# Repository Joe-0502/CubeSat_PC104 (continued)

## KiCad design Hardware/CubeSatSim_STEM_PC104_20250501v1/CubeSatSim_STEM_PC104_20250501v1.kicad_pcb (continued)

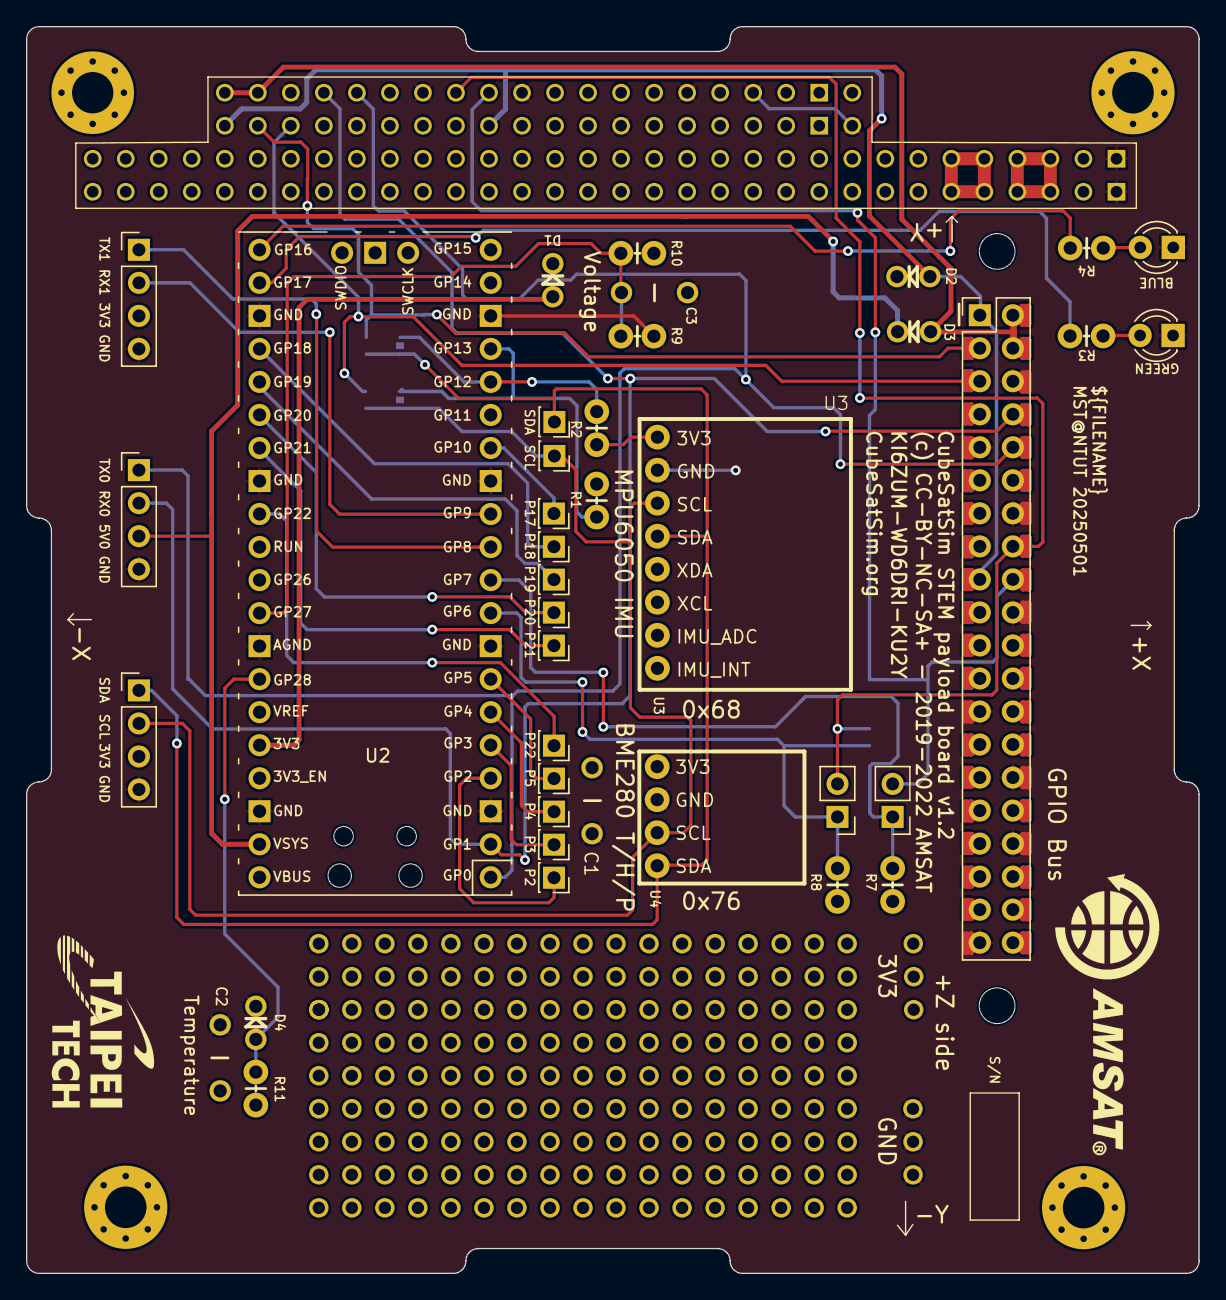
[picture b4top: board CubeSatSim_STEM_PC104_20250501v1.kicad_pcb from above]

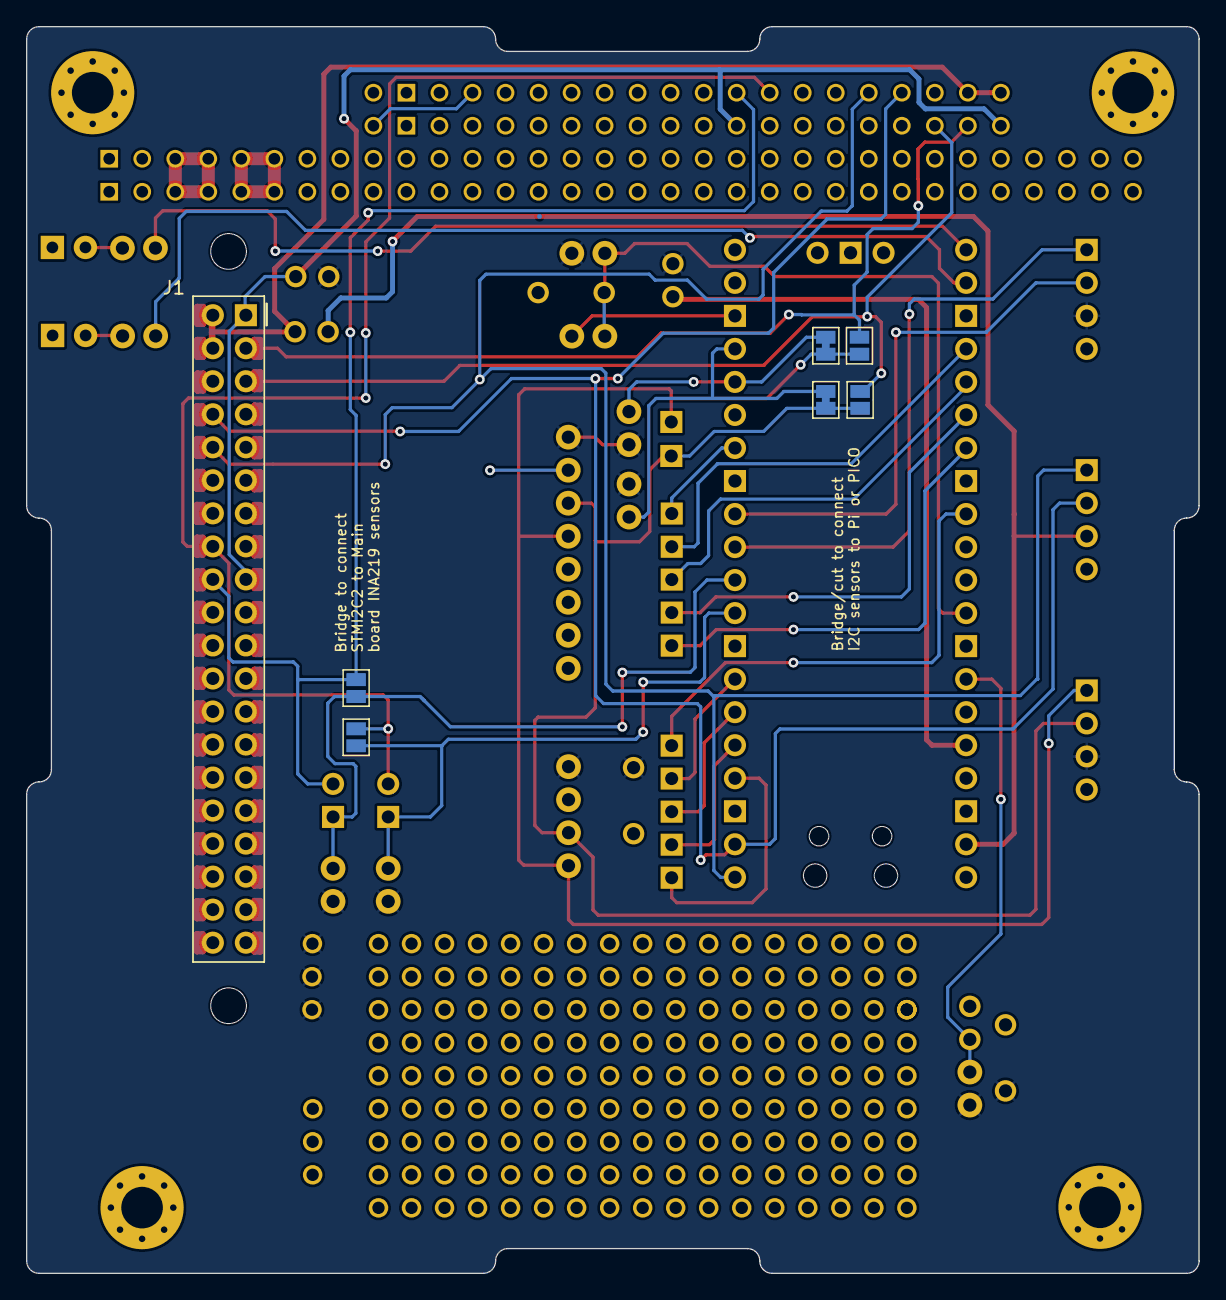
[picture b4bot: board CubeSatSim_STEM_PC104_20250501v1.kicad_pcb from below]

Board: 2 copper layers, 90.2 x 95.9 mm, 46 parts (6 on the bottom side), 38 nets.

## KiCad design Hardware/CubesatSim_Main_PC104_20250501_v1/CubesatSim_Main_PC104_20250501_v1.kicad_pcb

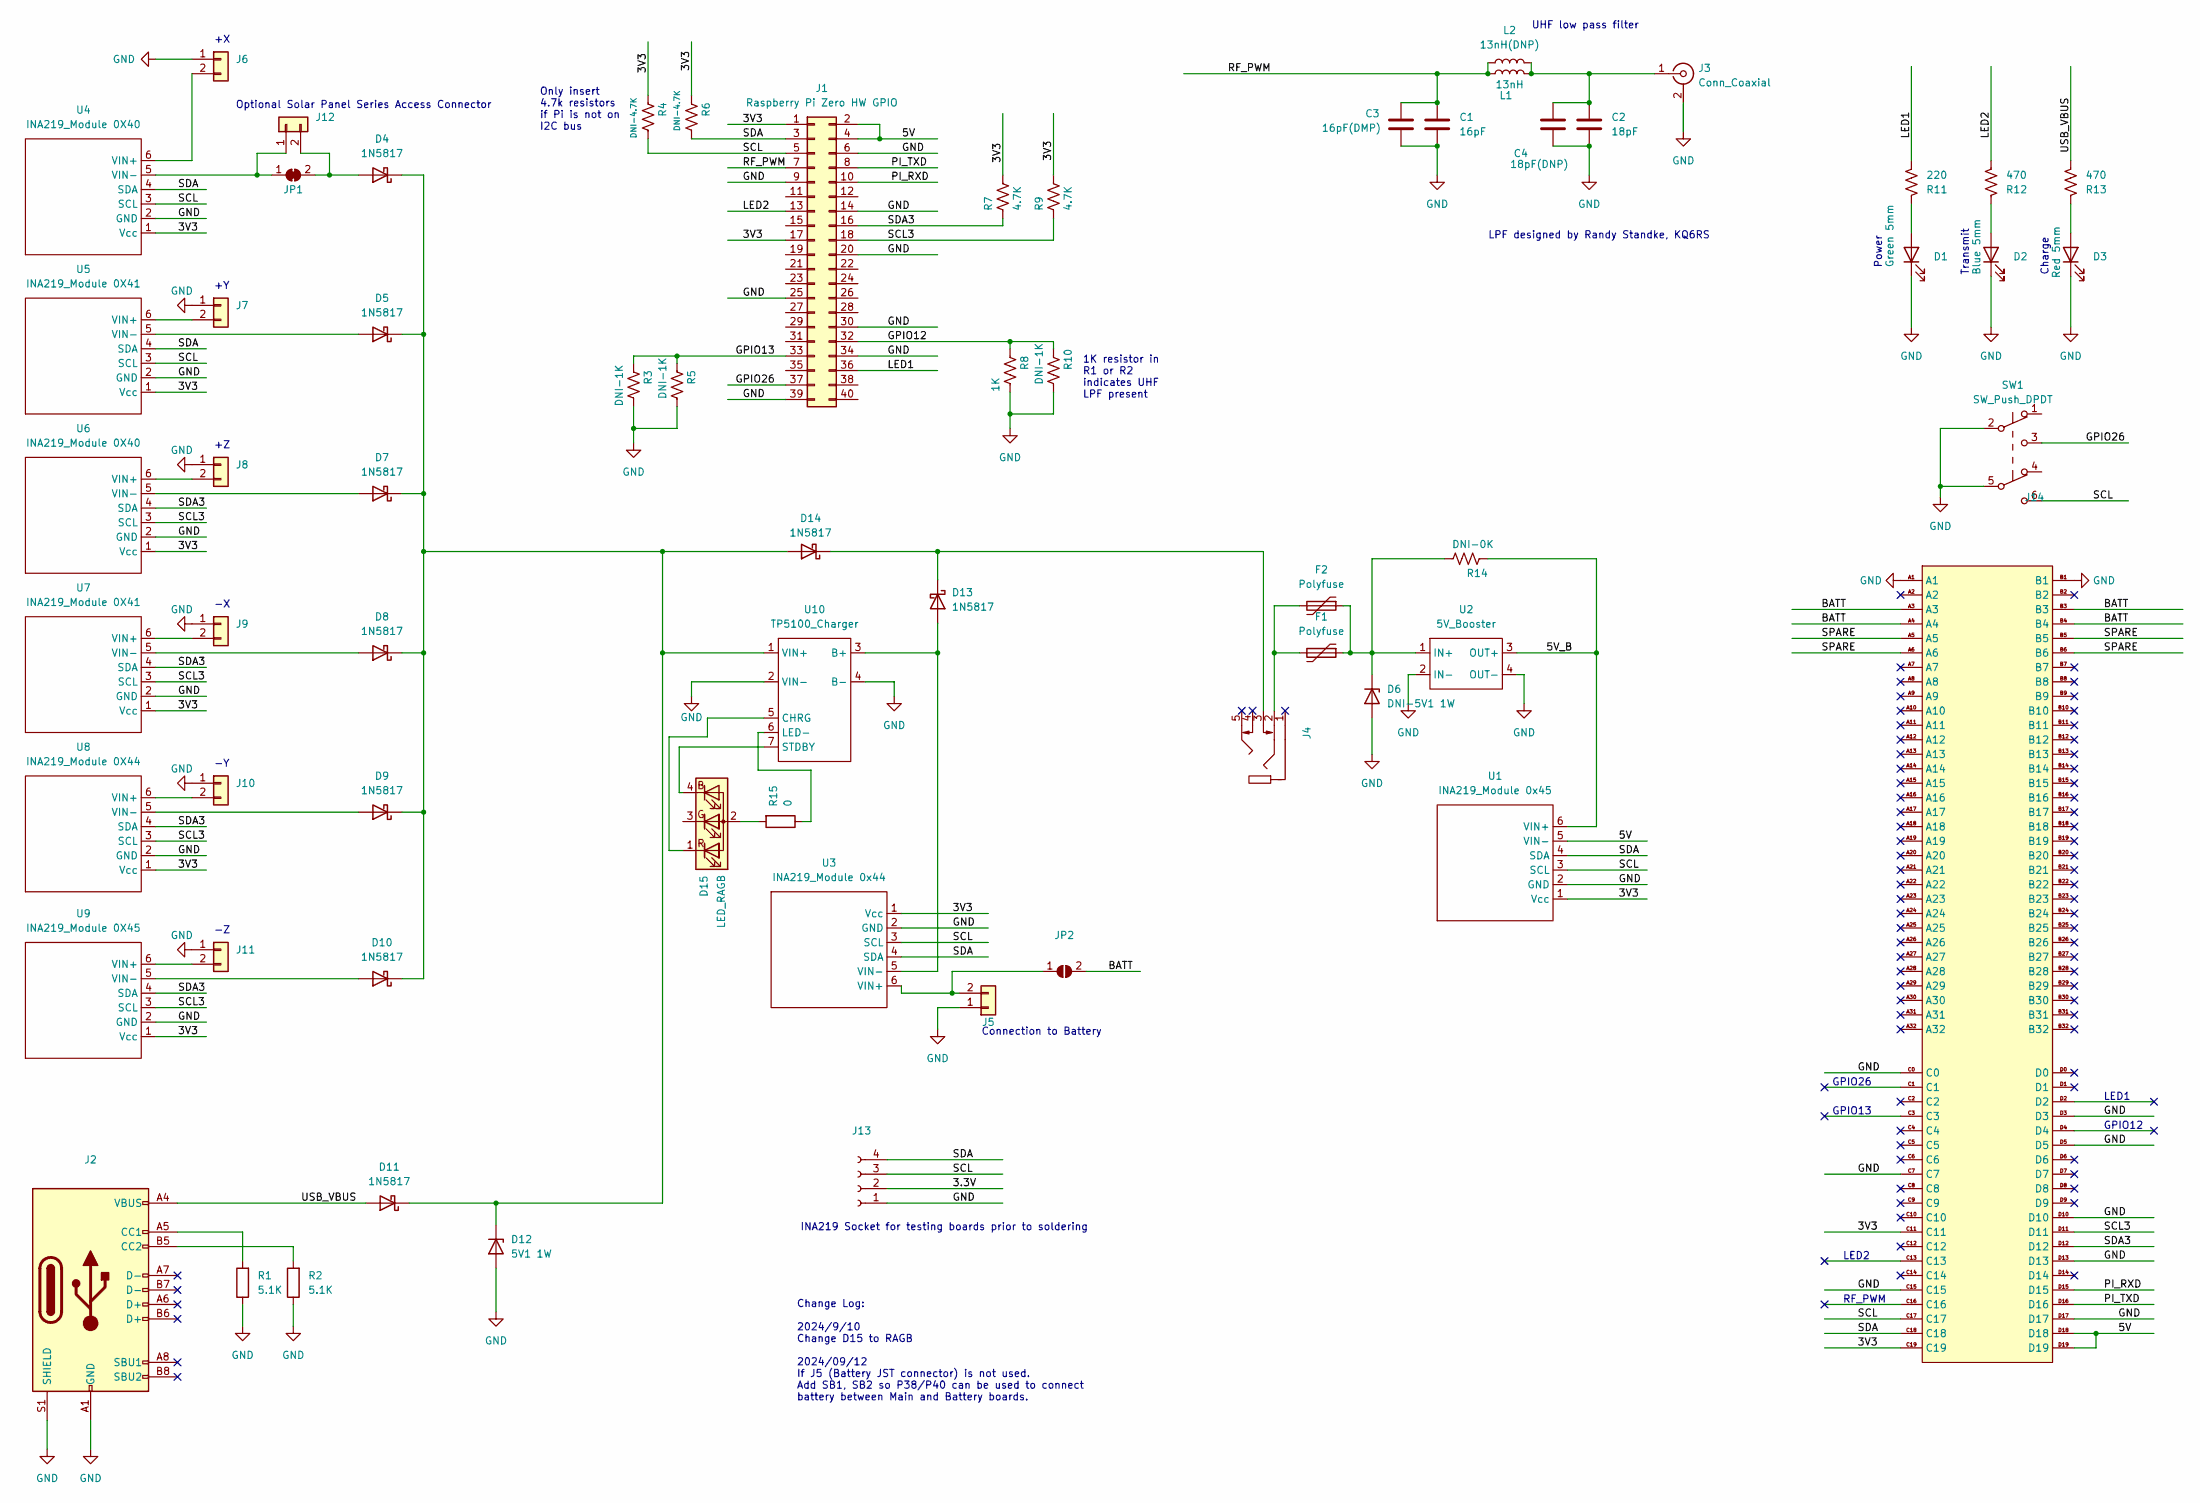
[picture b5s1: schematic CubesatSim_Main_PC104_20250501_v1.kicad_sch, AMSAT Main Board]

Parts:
C1: 16pF; C_0603_1608Metric
C2: 18pF; C_0603_1608Metric
C3: 16pF(DMP); C_0402_1005Metric
C4: 18pF(DNP); C_0402_1005Metric
D1: Green 5mm; LED_D5.0mm
D2: Blue 5mm; LED_D5.0mm
D3: Red 5mm; LED_D5.0mm
D4, D5, D7, D8, D9, D10, D11, D13, D14: 1N5817; SS14
D6: DNI-5V1 1W; 1N5817
D12: 5V1 1W; 1N5817
D15: LED_RAGB; LED_D5.0mm-4_RGB
F1: Polyfuse; Fuse_1812_4532Metric
F2: Polyfuse; AMSAT_PTC
J1: Raspberry Pi Zero HW GPIO; PinSocket_2x20_P2.54mm_Vertical
J2: USB_C_Receptacle_USB2.0; USB_C_Receptacle_GCT_USB4105-xx-A_16P_TopMnt_Horizontal
J3: Conn_Coaxial; AMSAT_SMA_Vertical
J4: AudioJack2_Dual_Ground_Switch; Jack_3.5mm_CUI_SJ1-3525N_Horizontal
J5, J6, J7, J8, J9, J10, J11, J12: Conn_01x02; JST_PH_B2B-PH-K_1x02_P2.00mm_Vertical
J13: Conn_01x04_Female; PinHeader_1x04_P2.54mm_Vertical
J14: CubeSat_PC104_16bit_footprint_Edge.Cut
JP1: SolderJumper_2_Bridged; SolderJumper-2_P1.3mm_Bridged_Pad1.0x1.5mm
JP2: SolderJumper_2_Open; SolderJumper_2_Tri_New
L1: 13nH; L_0603_1608Metric
L2: 13nH(DNP); L_0402_1005Metric
R1, R2: 5.1K; R_0603_1608Metric
R3: DNI-1K; R_Axial_DIN0204_L3.6mm_D1.6mm_P2.54mm_Vertical
R4, R6: DNI-4.7K; R_Axial_DIN0204_L3.6mm_D1.6mm_P2.54mm_Vertical
R5, R10: DNI-1K; R_0603_1608Metric
R7, R9: 4.7K; R_Axial_DIN0204_L3.6mm_D1.6mm_P2.54mm_Vertical
R8: 1K; R_Axial_DIN0204_L3.6mm_D1.6mm_P2.54mm_Vertical
R11: 220; R_Axial_DIN0204_L3.6mm_D1.6mm_P2.54mm_Vertical
R12, R13: 470; R_Axial_DIN0204_L3.6mm_D1.6mm_P2.54mm_Vertical
R14: DNI-0K; R_0805_2012Metric
R15: 0; R_0603_1608Metric
SW1: SW_Push_DPDT; SW_Push_2P2T_Vertical_E-Switch_800UDP8P1A1M6
U1: INA219_Module 0x45; INA219_Small
U2: 5V_Booster; 5V_BOOSTER
U3: INA219_Module 0x44; INA219_Small
U4, U6: INA219_Module 0X40; INA219_Small
U5, U7: INA219_Module 0X41; INA219_Small
U8: INA219_Module 0X44; INA219_Small
U9: INA219_Module 0X45; INA219_Small
U10: TP5100_Charger; TP5100 Charger_SMD

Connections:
/3.3V: J13.2
/3V3: J1.1, J1.17, J14.C11, J14.C19, R4.1, R6.1, R7.1, R9.1, U1.1 (Vcc), U3.1 (Vcc), U4.1 (Vcc), U5.1 (Vcc), U6.1 (Vcc), U7.1 (Vcc), U8.1 (Vcc), U9.1 (Vcc)
/5V: J1.2, J1.4, J14.D18, J14.D19, U1.5 (VIN-)
/5V_B: R14.1, U1.6 (VIN+), U2.3 (OUT+)
/BATT: J14.A3, J14.A4, J14.B3, J14.B4, JP2.2 (B)
/GPIO12: J1.32, R8.1, R10.1
/GPIO13: J1.33, R3.1, R5.1
/GPIO26: J1.37, SW1.3 (C)
/LED1: J1.36, R11.2
/LED2: J1.13, R12.2
/PI_RXD: J1.10, J14.D15
/PI_TXD: J1.8, J14.D16
/RF_PWM: C1.1, C3.1, J1.7, L1.1, L2.1
/SCL: J1.5, J13.3, J14.C17, R4.2, SW1.6 (C), U1.3 (SCL), U3.3 (SCL), U4.3 (SCL), U5.3 (SCL)
/SCL3: J1.18, J14.D11, R9.2, U6.3 (SCL), U7.3 (SCL), U8.3 (SCL), U9.3 (SCL)
/SDA: J1.3, J13.4, J14.C18, R6.2, U1.4 (SDA), U3.4 (SDA), U4.4 (SDA), U5.4 (SDA)
/SDA3: J1.16, J14.D12, R7.2, U6.4 (SDA), U7.4 (SDA), U8.4 (SDA), U9.4 (SDA)
/SPARE: J14.A5, J14.A6, J14.B5, J14.B6
/USB_VBUS: D11.2 (A), J2.A4 (VBUS), J2.A9 (VBUS), J2.B4 (VBUS), J2.B9 (VBUS), R13.2; also elsewhere on the board
GND: C1.2, C2.2, C3.2, C4.2, D1.1 (K), D2.1 (K), D3.1 (K), D6.2 (A), D12.2 (A), J1.6, J1.9, J1.14, J1.20, J1.25, J1.30, J1.34, J1.39, J2.A1 (GND), J2.A12 (GND), J2.B1 (GND), J2.B12 (GND), J2.S1 (SHIELD), J3.2 (Ext), J5.1, J6.1, J7.1, J8.1, J9.1, J10.1, J11.1, J13.1, J14.A1, J14.B1, J14.C0, J14.C7, J14.C15, J14.D3, J14.D5, J14.D10, J14.D13, J14.D17, R1.1, R2.1, R3.2, R5.2, R8.2, R10.2, SW1.2 (B), SW1.5 (B), U1.2 (GND), U2.2 (IN-), U2.4 (OUT-), U3.2 (GND), U4.2 (GND), U5.2 (GND), U6.2 (GND), U7.2 (GND), U8.2 (GND), U9.2 (GND), U10.2 (VIN-), U10.4 (B-); also elsewhere on the board
unnamed: D1.2 (A), R11.1
unnamed: D2.2 (A), R12.1
unnamed: D3.2 (A), R13.1
unnamed: D4.2 (A), J12.2, JP1.2 (B)
unnamed: D5.2 (A), U5.5 (VIN-)
unnamed: D6.1 (K), F1.1, F2.1, R14.2, U2.1 (IN+)
unnamed: D7.2 (A), U6.5 (VIN-)
unnamed: D8.2 (A), U7.5 (VIN-)
unnamed: D9.2 (A), U8.5 (VIN-)
unnamed: D10.2 (A), U9.5 (VIN-)
unnamed: D4.1 (K), D5.1 (K), D7.1 (K), D8.1 (K), D9.1 (K), D10.1 (K), D11.1 (K), D12.1 (K), D14.2 (A), U10.1 (VIN+)
unnamed: D13.2 (A), U3.5 (VIN-), U10.3 (B+)
unnamed: D13.1 (K), D14.1 (K), J4.3
unnamed: D15.2 (A), R15.2
unnamed: D15.4 (BK), U10.7 (STDBY)
unnamed: D15.1 (RK), U10.5 (CHRG)
unnamed: F1.2, F2.2, J4.2
unnamed: J2.A5 (CC1), R1.2
unnamed: J2.B5 (CC2), R2.2
unnamed: C2.1, C4.1, J3.1 (In), L1.2, L2.2
unnamed: J5.2, JP2.1 (A), U3.6 (VIN+)
unnamed: J6.2, U4.6 (VIN+)
unnamed: J7.2, U5.6 (VIN+)
unnamed: J8.2, U6.6 (VIN+)
unnamed: J9.2, U7.6 (VIN+)
unnamed: J10.2, U8.6 (VIN+)
unnamed: J11.2, U9.6 (VIN+)
unnamed: J12.1, JP1.1 (A), U4.5 (VIN-)
unnamed: R15.1, U10.6 (LED-)

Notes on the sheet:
GPIO26
Power
Change Log: 2024/9/10 Change D15 to RAGB 2024/09/12 If J5 (Battery JST connector) is not used. Add SB1, SB2 so P38/P40 can be used to connect battery between Main and Battery boards.
LED1
LPF designed by Randy Standke, KQ6RS
UHF low pass filter
RF_PWM
Optional Solar Panel Series Access Connector
Transmit
INA219 Socket for testing boards prior to soldering
LED2
GPIO12
1K resistor in R1 or R2 indicates UHF LPF present
Only insert 4.7k resistors if Pi is not on I2C bus
Charge
Connection to Battery
GPIO13

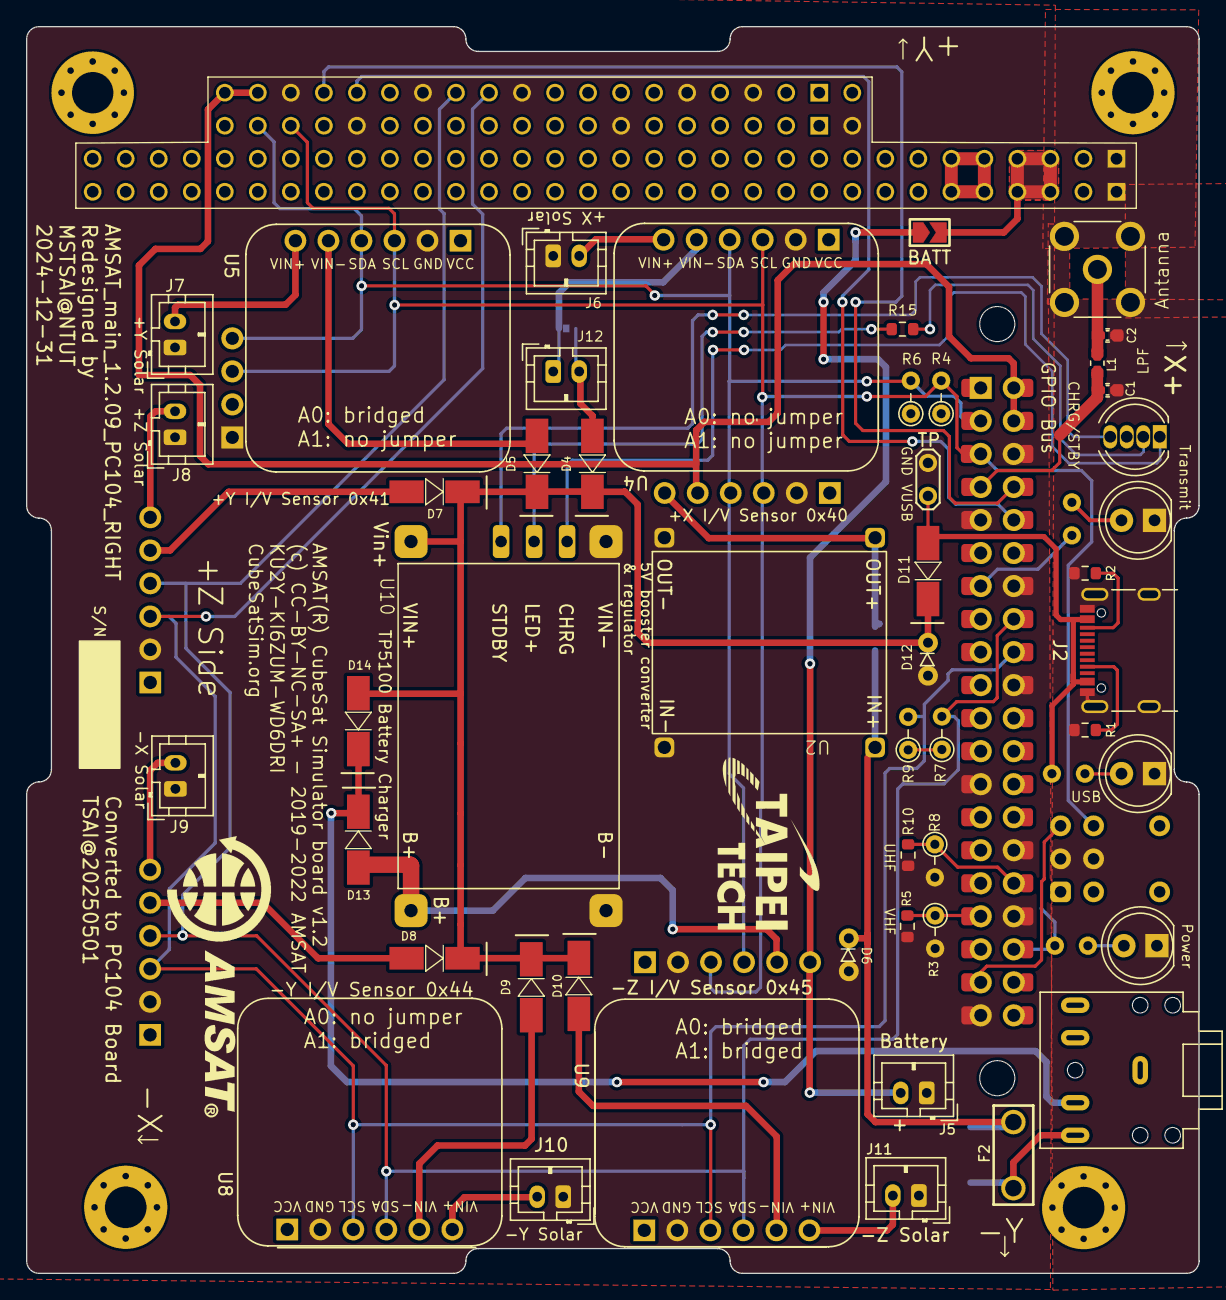
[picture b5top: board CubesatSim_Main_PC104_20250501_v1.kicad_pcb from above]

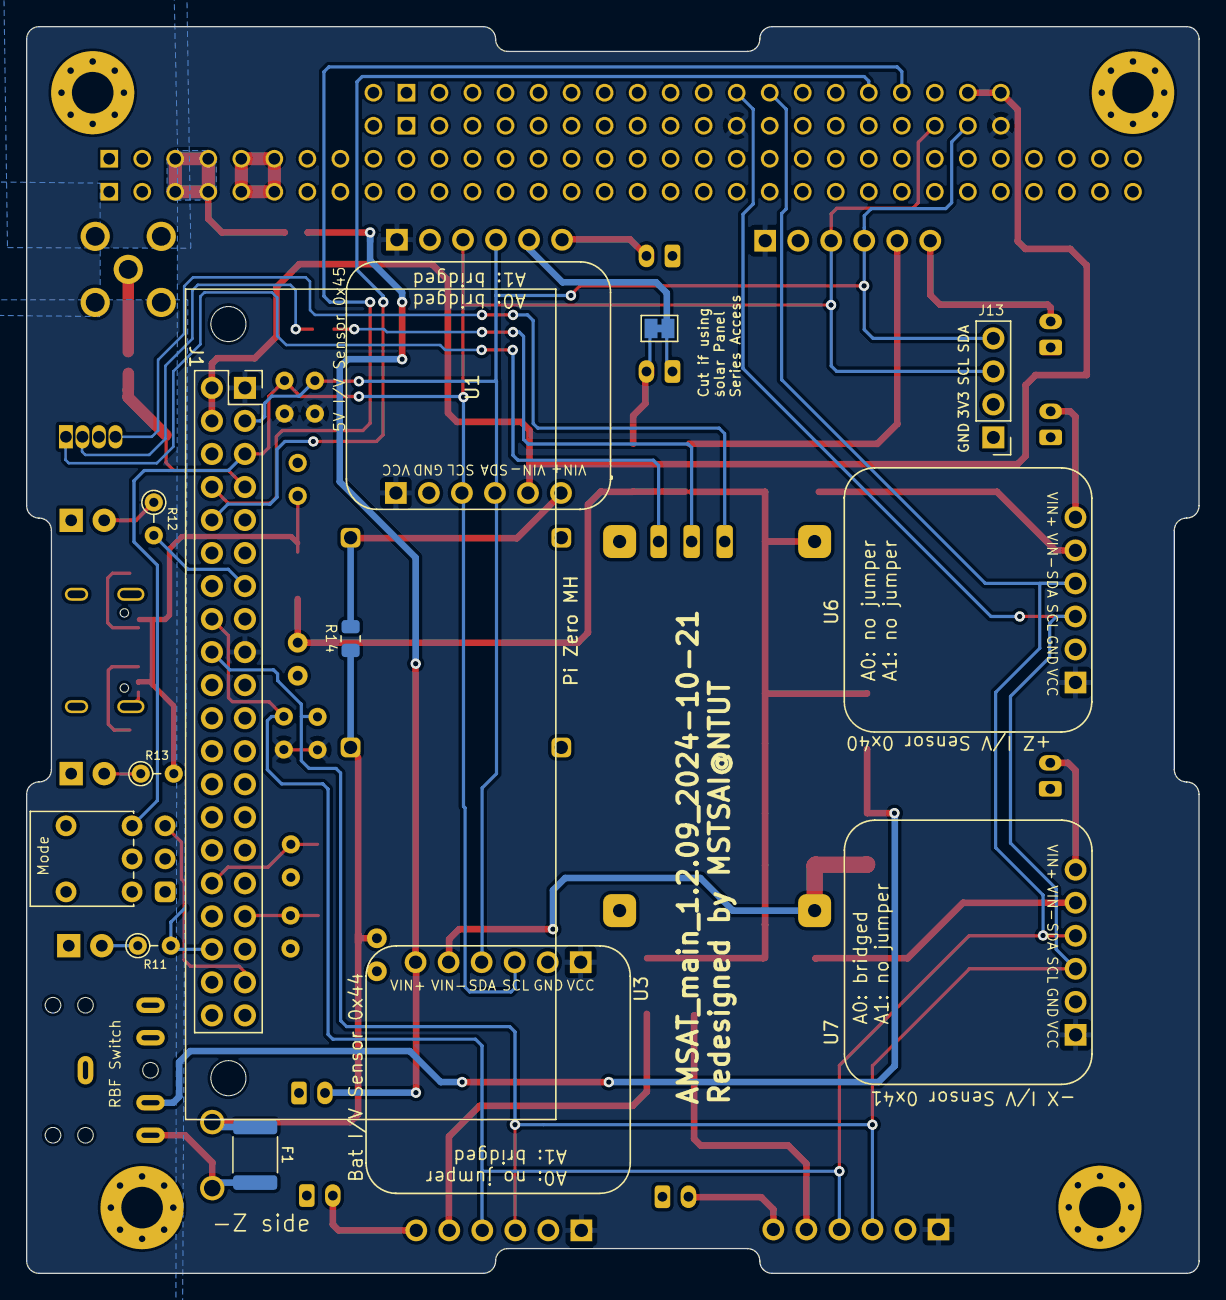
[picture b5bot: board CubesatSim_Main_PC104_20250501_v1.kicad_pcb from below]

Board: 2 copper layers, 90.2 x 95.9 mm, 66 parts (13 on the bottom side), 48 nets.

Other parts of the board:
TP: TestPoint_2Pads_Pitch2.54mm_Drill0.8mm

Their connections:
/USB_VBUS: TP.1; also elsewhere on the board
GND: TP.2; also elsewhere on the board

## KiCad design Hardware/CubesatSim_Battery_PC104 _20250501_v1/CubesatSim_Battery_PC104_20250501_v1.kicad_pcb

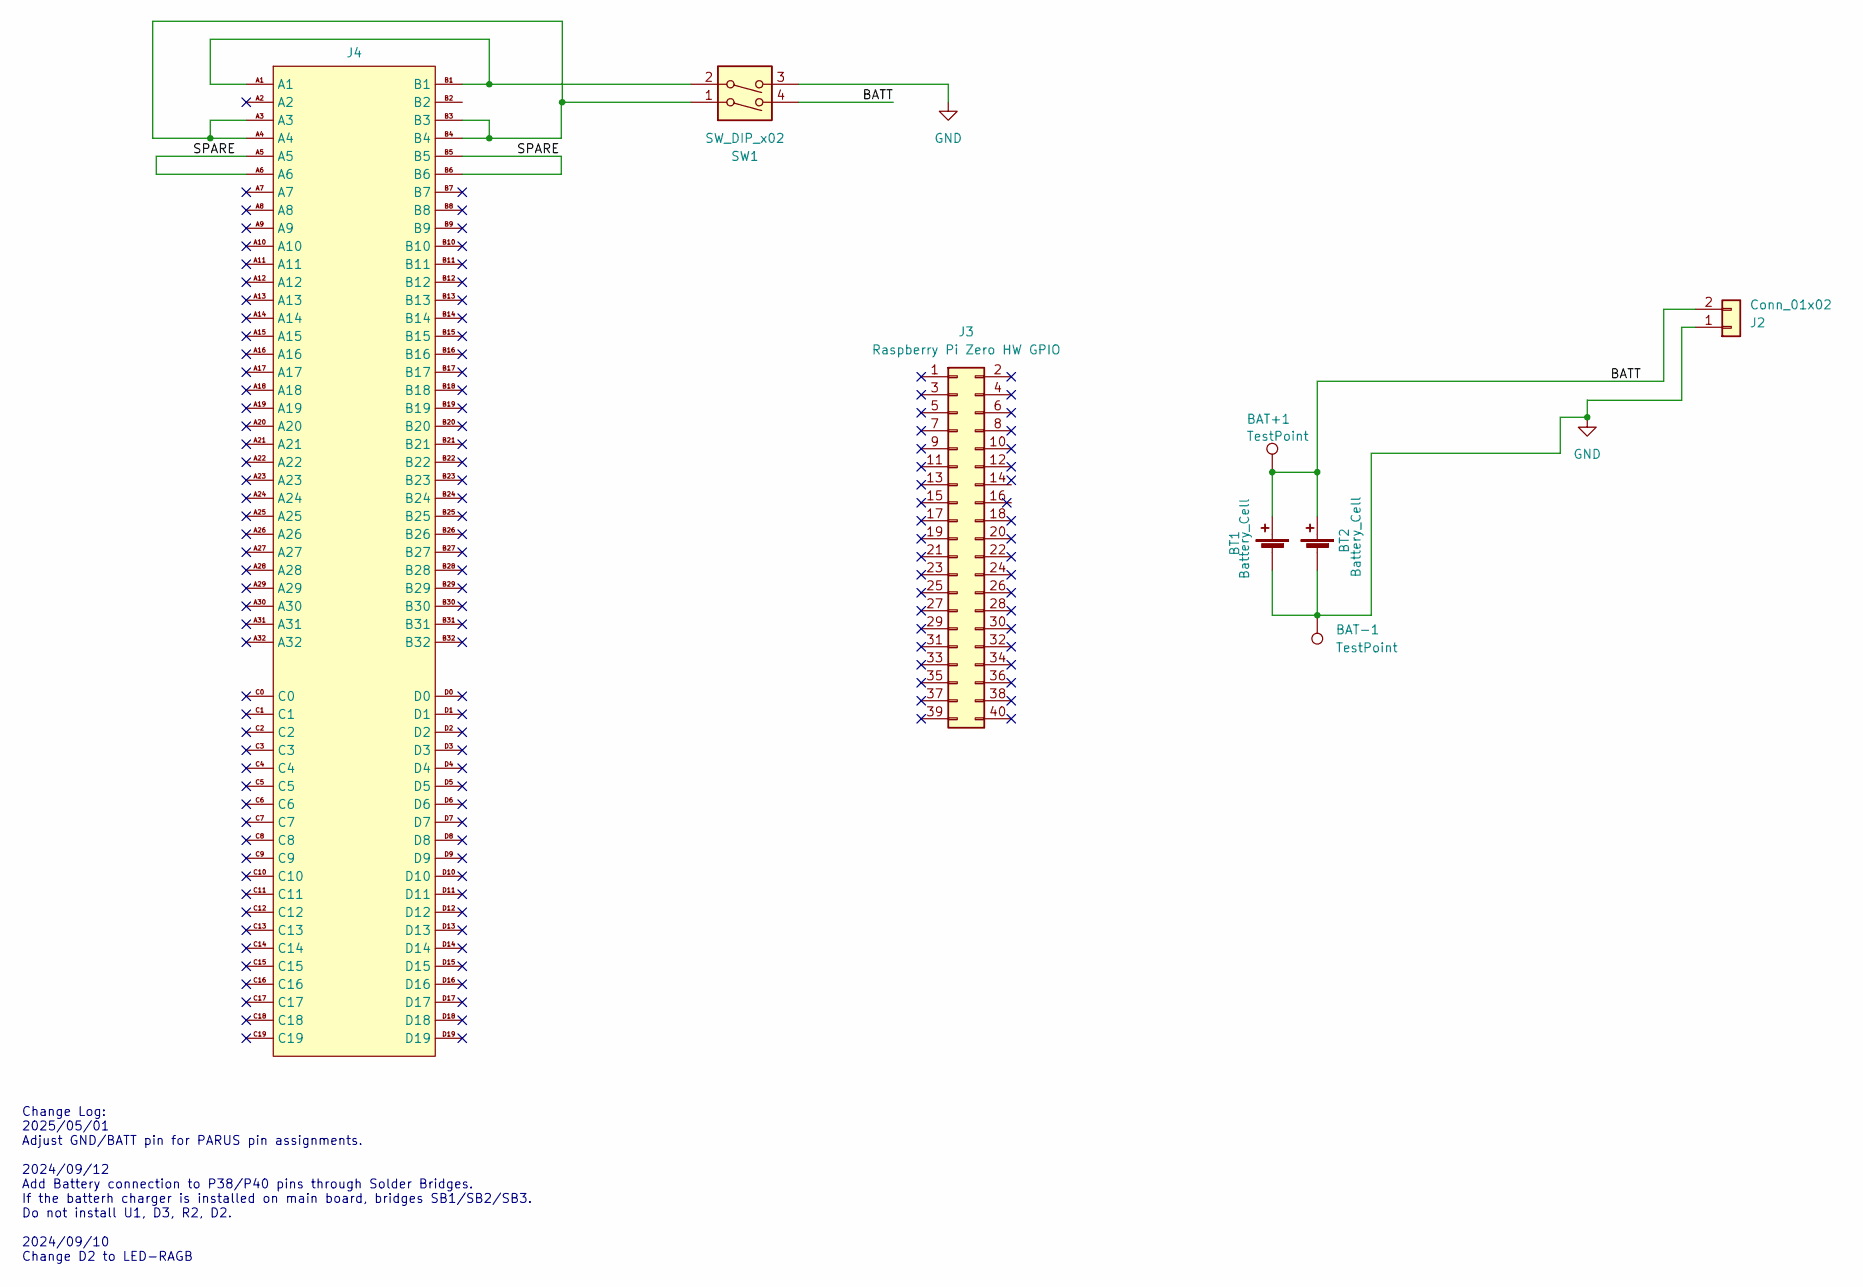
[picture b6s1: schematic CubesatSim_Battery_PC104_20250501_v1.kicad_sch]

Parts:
BAT+1: TestPoint; TestPoint_THTPad_2.0x2.0mm_Drill1.0mm
BAT-1: TestPoint; TestPoint_THTPad_2.0x2.0mm_Drill1.0mm
BT1, BT2: Battery_Cell; BatteryHolder_MPD_BH-18650-PC2
J2: Conn_01x02; JST_PH_B2B-PH-K_1x02_P2.00mm_Vertical
J3: Raspberry Pi Zero HW GPIO; PinSocket_2x20_P2.54mm_Vertical
J4: CubeSat_PC104_16bit_footprint_Edge.Cut
SW1: SW_DIP_x02; SW_DIP_SPSTx02_Piano_10.8x6.64mm_W7.62mm_P2.54mm

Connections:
/BATT: BAT+1.1, BT1.1 (+), BT2.1 (+), J2.2, SW1.4
/SPARE: J4.A5, J4.A6, J4.B5, J4.B6
GND: BAT-1.1, BT1.2 (-), BT2.2 (-), J2.1, SW1.3
unnamed: J4.A1, J4.B1, SW1.2
unnamed: J4.A3, J4.A4, J4.B3, J4.B4, SW1.1

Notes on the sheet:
Change Log: 2025/05/01 Adjust GND/BATT pin for PARUS pin assignments. 2024/09/12 Add Battery connection to P38/P40 pins through Solder Bridges. If the batterh charger is installed on main board, bridges SB1/SB2/SB3. Do not install U1, D3, R2, D2. 2024/09/10 Change D2 to LED-RAGB

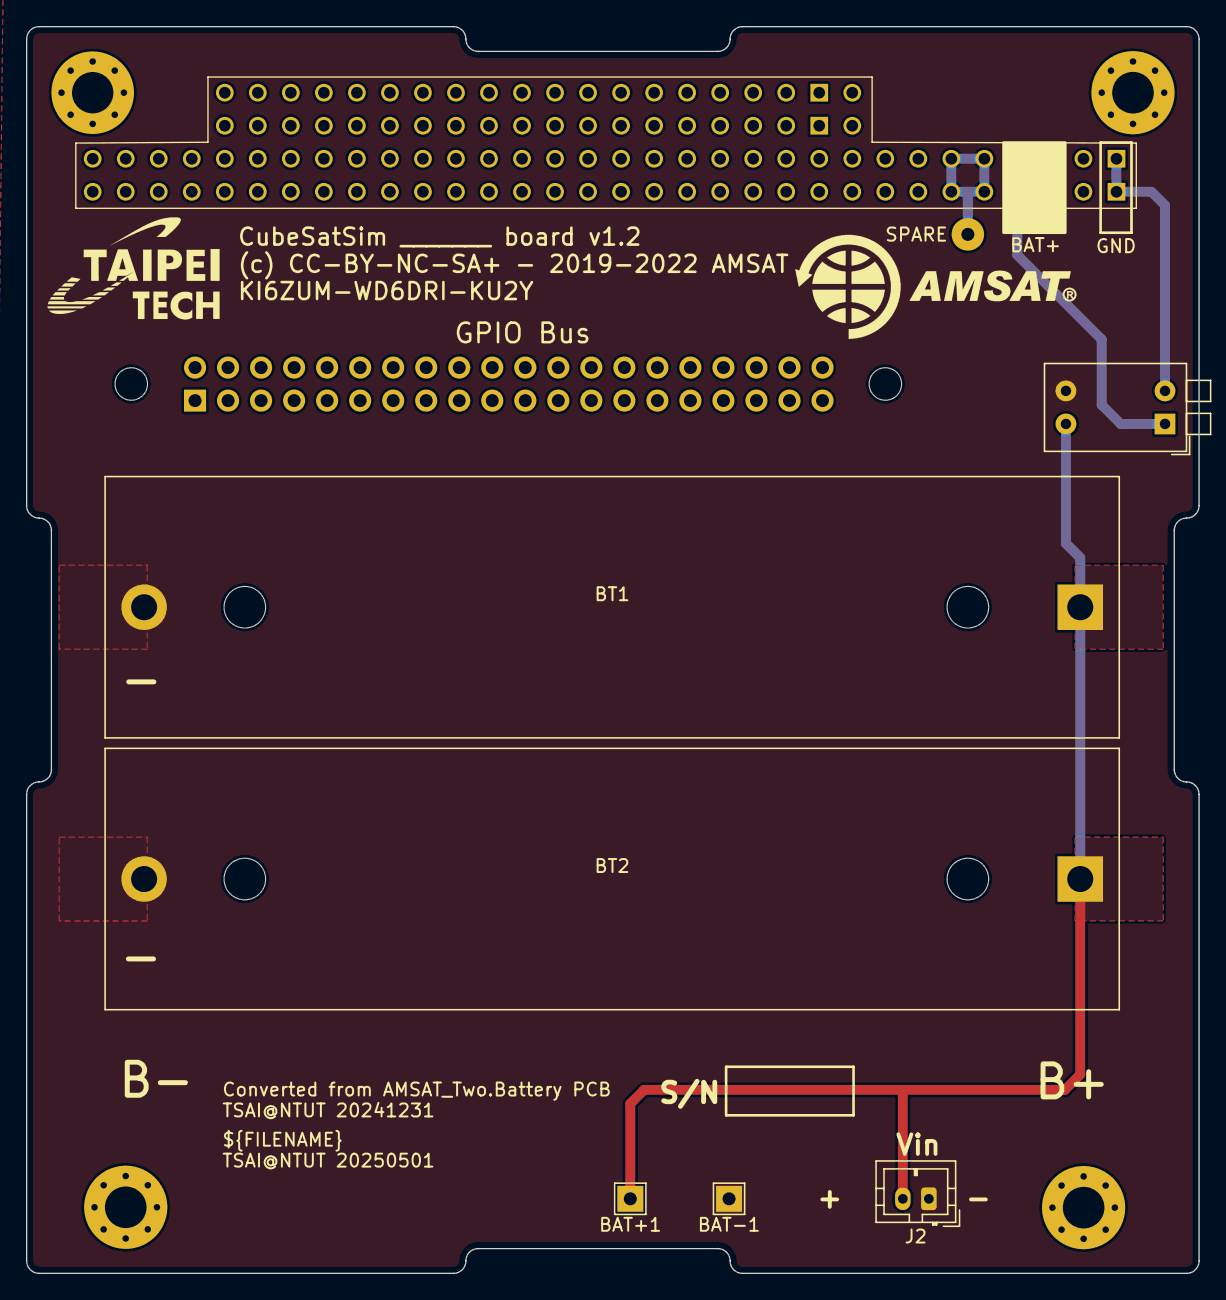
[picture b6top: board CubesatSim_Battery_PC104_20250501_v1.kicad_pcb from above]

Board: 2 copper layers, 90.2 x 95.9 mm, 8 parts (1 on the bottom side), 5 nets.

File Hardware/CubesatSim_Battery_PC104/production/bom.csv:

Designator,Footprint,Quantity,Value,LCSC Part #
"BAT+1, BAT-1",TestPoint_THTPad_2.0x2.0mm_Drill1.0mm,2,TestPoint,
"BT1, BT2",BatteryHolder_MPD_BH-18650-PC2,2,Battery_Cell,
J2,JST_PH_B2B-PH-K_1x02_P2.00mm_Vertical,1,Conn_01x02,
J3,PinSocket_2x20_P2.54mm_Vertical,1,Raspberry Pi Zero HW GPIO,
J4,CubeSat_PC104_16bit_footprint_Edge.Cut,1,~,
SB3,SolderJumper-2_P1.3mm_Open_Pad1.0x1.5mm,1,SolderJumper_2_Open,
SW1,SW_DIP_SPSTx02_Piano_10.8x6.64mm_W7.62mm_P2.54mm,1,SW_DIP_x02,

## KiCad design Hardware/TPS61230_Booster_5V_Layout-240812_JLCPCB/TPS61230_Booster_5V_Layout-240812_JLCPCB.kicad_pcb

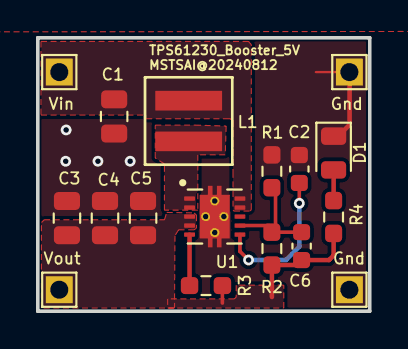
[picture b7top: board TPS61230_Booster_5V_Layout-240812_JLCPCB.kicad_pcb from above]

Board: 2 copper layers, 18.4 x 15.2 mm, 17 parts (0 on the bottom side), 8 nets.

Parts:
C1, C3, C4, C5: 22uF; C_0805_2012Metric
C2: 10nF; C_0603_1608Metric
C6: DNI/18pF; C_0603_1608Metric
D1: LED; LED_0805_2012Metric
L1: 1uH; IND_EXLA-0402_EAT
R1: 100K; R_0603_1608Metric_Pad0.98x0.95mm_HandSolder
R2: 402K; R_0603_1608Metric_Pad0.98x0.95mm_HandSolder
R3: 1M0; R_0603_1608Metric_Pad0.98x0.95mm_HandSolder
R4: 1K; R_0603_1608Metric_Pad0.98x0.95mm_HandSolder
TP5: VIN; TestPoint_THTPad_1.5x1.5mm_Drill0.7mm
TP6, TP8: GND; TestPoint_THTPad_1.5x1.5mm_Drill0.7mm
TP7: VOUT; TestPoint_THTPad_1.5x1.5mm_Drill0.7mm
U1: VREG_V62_16624-01YE_TPS61230DRCR; TPS61230DRCR

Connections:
/FB: C6.2, R1.1, R2.2, U1.7 (FB)
/VIN: C1.1, L1.1, TP5.1, U1.9 (EN), U1.10 (VIN)
GND: C1.2, C2.2, C3.2, C4.2, C5.2, D1.1 (K), R1.2, TP6.1, TP8.1, U1.11 (GND), U1.12 (GND), U1.13 (GND), U1.14 (GND), U1.15
unnamed: D1.2 (A), R4.2
unnamed: R3.2, U1.5 (PG)
unnamed: C2.1, U1.6 (SS)
unnamed: L1.2, U1.1 (SW), U1.2 (SW__1)
unnamed: C3.1, C4.1, C5.1, C6.1, R2.1, R3.1, R4.1, TP7.1, U1.3 (VOUT), U1.4 (VOUT__1)
